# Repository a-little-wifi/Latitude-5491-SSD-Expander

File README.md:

# Latitude 5491 SSD Expander
This project is a PCB meant to fit in the large empty space around the Dell Latitude 5491's M.2 SSD slot. Together with a firmware modification, it should allow me to fit 2 2280 NVMe SSDs with 2 PCIe lanes each.

This is also an experiment to figure out PCIe bifurcation in general. In this case I'm using a Renesas 9ZXL0651AKLF clock buffer with 6 outputs, but I'm only using the first 2 for this board.

Should in theory also work on the H-class CPU version of the Latitude 5480, but not the U-class 5480 and 5490, those only have 2 PCIe lanes for the SSD slot in the first place.

~~Impedance is tuned for Aisler's 4-layer 0.8mm process~~ (thanks [Aisler](https://aisler.net/) for sponsoring the fabrication of this board!)  
Turns out the impedance and possibly other factors are not quite right, the current design has issues maintaining the PCIe link on the first slot, be aware if you plan to use this design.

### pics:

> 
> 

> 
> 

# Results:

## It works!
> 

> Bifurcation board with 2 SSDs installed in a Latitude 5491

> 

> Both SSDs showing up in the setup menu (the second one is showing in the entry usually meant for the WWAN slot lol)

> 

> Both SSDs detected in Gnome Disks (Ubuntu 16.04 live)

> 

> Both SSDs showing up in lspci (not shown: both running at PCIe x2 as expected)

## How to make it work:

To get this working, you need to modify the Flex I/O configuration of your laptop by dumping the content of the BIOS chip, loading it into Intel's Flash Image Tool (mfit) (version 12.0.85.1919 for the Latitude 5491), navigating to the Flex I/O section and changing the PCIe Port Configuration for PCIe Controller 3 (Port 9-12) (this is the one connected to the M-key slot on the 5491) from 1x4 to 2x2:

> 

> Changing the PCIe port from 1x4 to 2x2 in mfit

Then click the Build Image button at the top of the mfit window to generate a new bios binary file that can be flashed back onto the laptop (outimage.bin in the same directory as fit.exe)

For your first boot you might need to clear the cmos to get it to run and also give it a few reboot cycles. 

## I provide no warranty on any of this, I am not responsible if you mess up your machine  
This is only an experiment to prove it's possible for end users to bifurcate and generally change the configuration of the PCH PCIe lanes in their Intel-based laptop

For the next bifurcation adapter I'll probably use the Renesas 9DBL411BGLFT clock buffer instead, looks easier to solder and is readily available

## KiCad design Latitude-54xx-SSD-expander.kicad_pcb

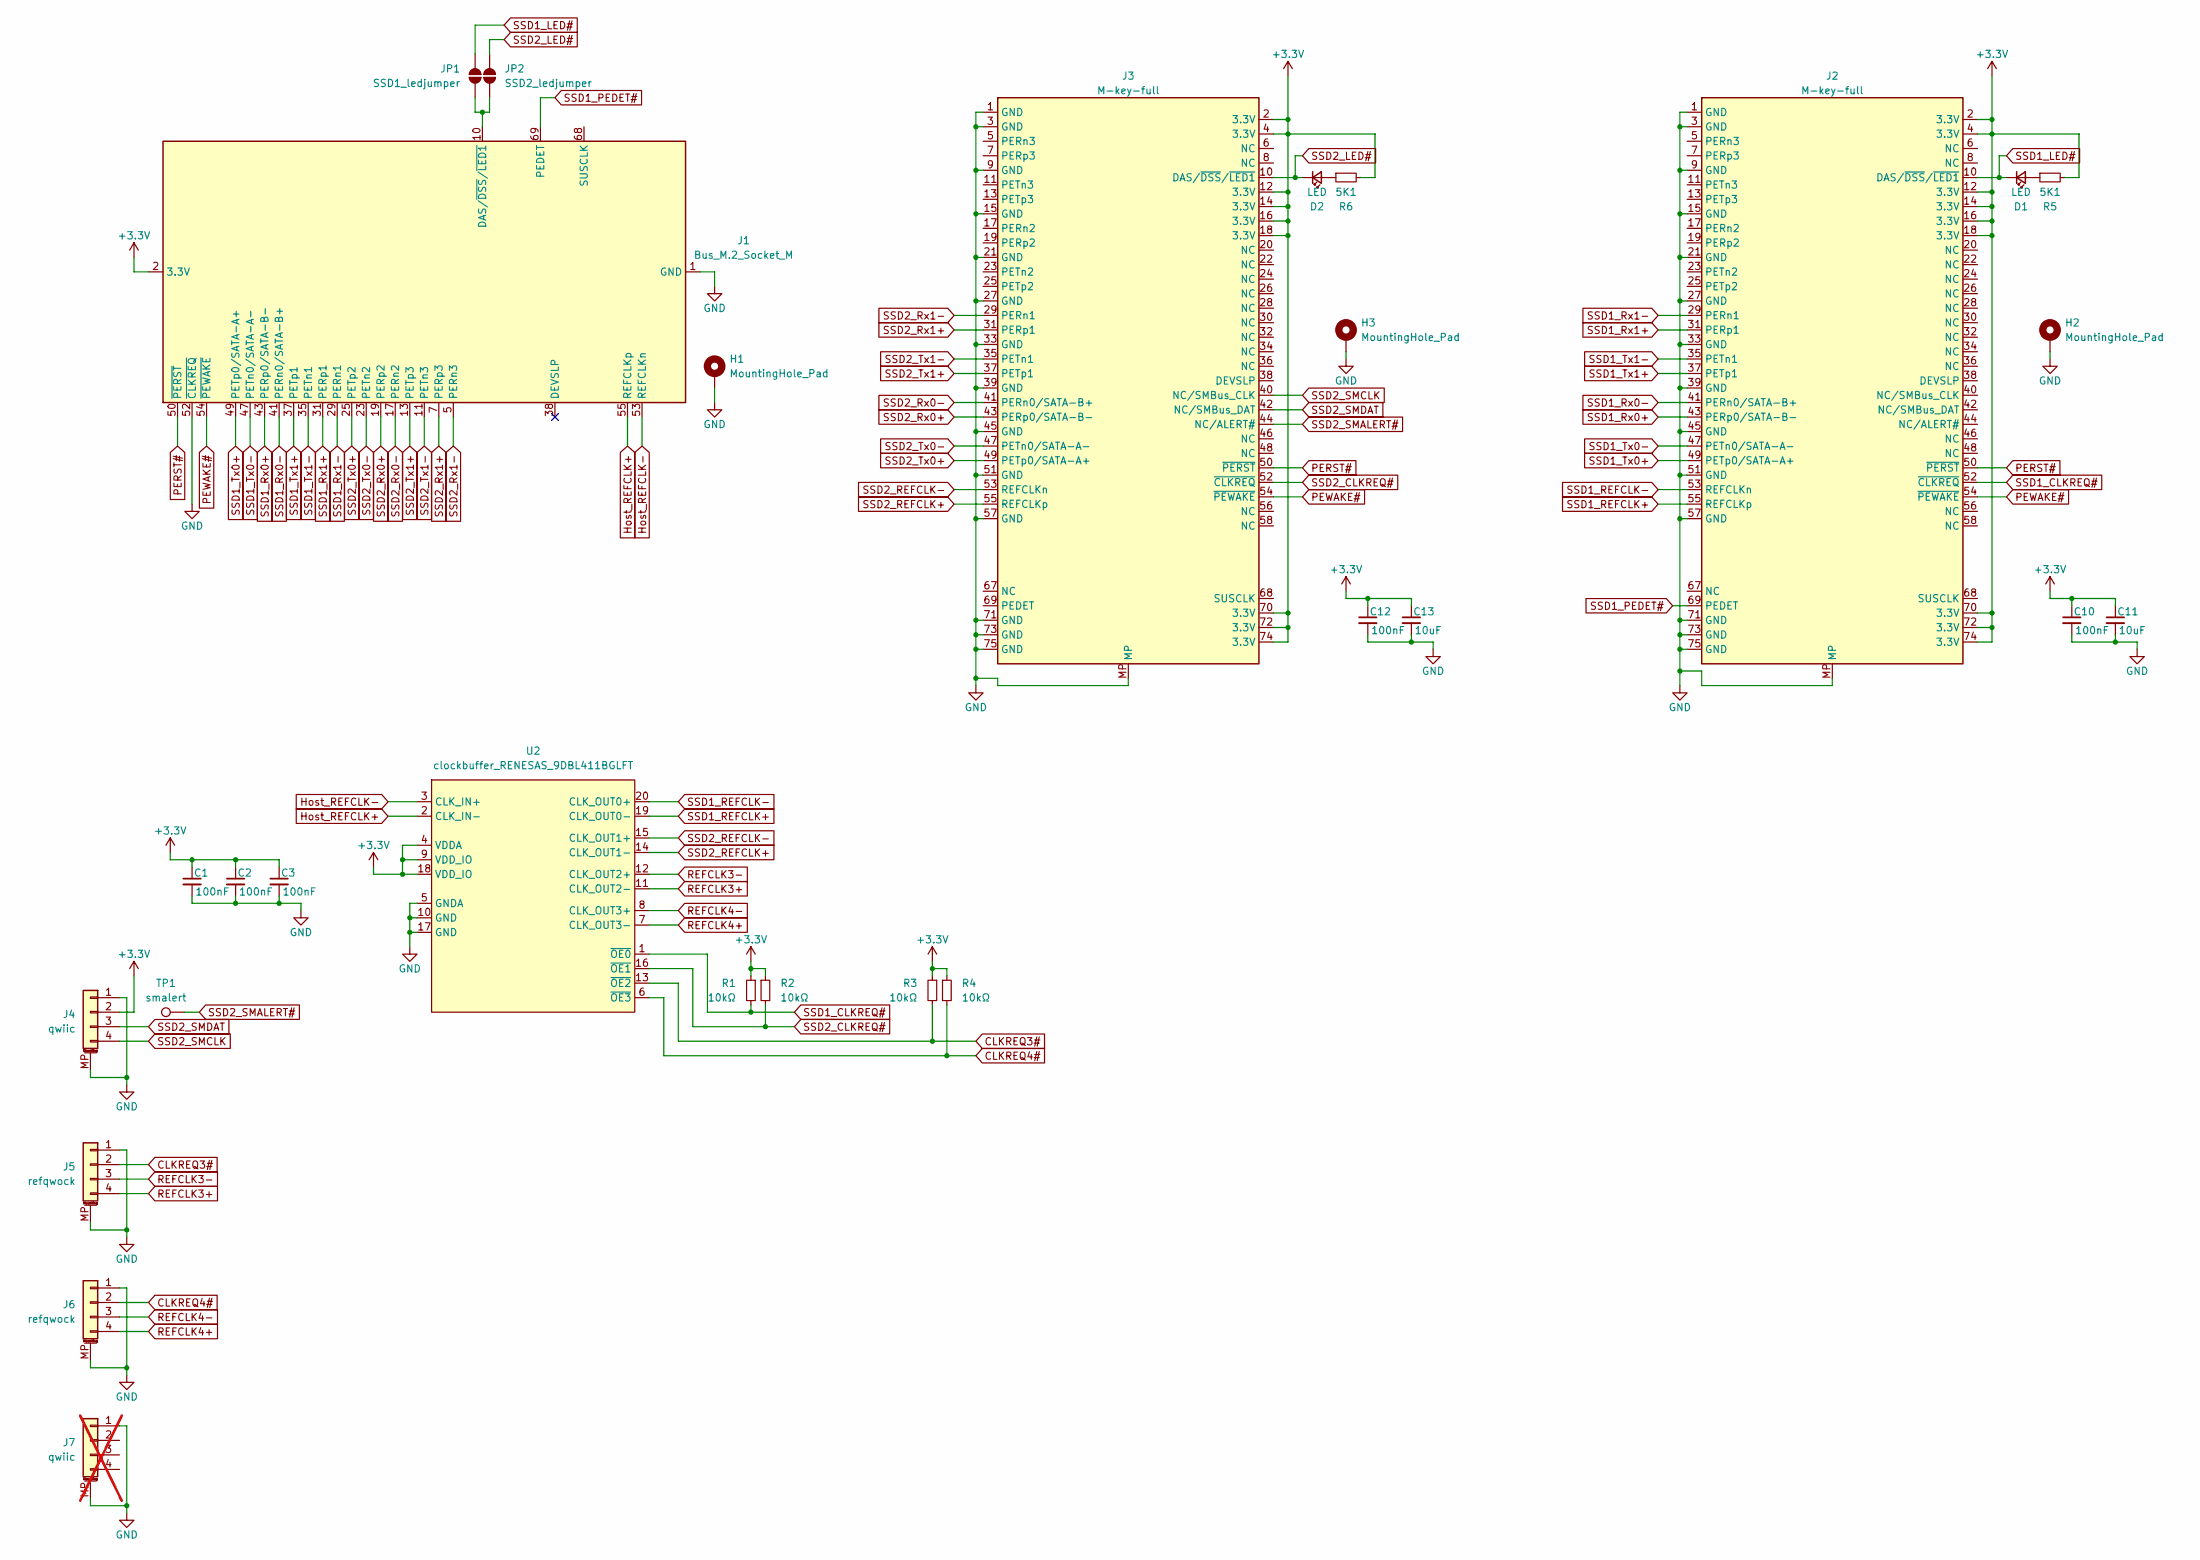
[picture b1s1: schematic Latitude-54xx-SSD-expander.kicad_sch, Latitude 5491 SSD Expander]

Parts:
C1, C2, C3, C10, C12: 100nF; C_0603_1608Metric
C11, C13: 10uF; C_0603_1608Metric
D1, D2: LED; D_0603_1608Metric
H1: MountingHole_Pad; MountingHole_3.5mm_Pad
H2, H3: MountingHole_Pad; MountingHole_4mm_Pad
J1: Bus_M.2_Socket_M; NGFF_M
J2, J3: M-key-full; m-key
J4: qwiic; JST_SH_SM04B-SRSS-TB_1x04-1MP_P1.00mm_Horizontal
J5, J6: refqwock; JST_SH_SM04B-SRSS-TB_1x04-1MP_P1.00mm_Horizontal
J7: qwiic; JST_SH_SM04B-SRSS-TB_1x04-1MP_P1.00mm_Horizontal; not fitted
JP1: SSD1_ledjumper; mySolderJumper-1x0.5mm
JP2: SSD2_ledjumper; mySolderJumper-1x0.5mm
R1, R2, R3, R4: 10kΩ; R_0603_1608Metric
R5, R6: 5K1; R_0603_1608Metric
TP1: smalert; TestPoint_Pad_D1.0mm
U2: clockbuffer_RENESAS_9DBL411BGLFT; clockbuffer_RENESAS 9DBL411BGLFT; LCSC Part C2649348

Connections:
+3.3V: C1.1, C2.1, C3.1, C10.1, C11.1, C12.1, C13.1, J1.2 (3.3V), J1.4 (3.3V), J1.12 (3.3V), J1.14 (3.3V), J1.16 (3.3V), J1.18 (3.3V), J1.70 (3.3V), J1.72 (3.3V), J1.74 (3.3V), J2.2 (3.3V), J2.4 (3.3V), J2.12 (3.3V), J2.14 (3.3V), J2.16 (3.3V), J2.18 (3.3V), J2.70 (3.3V), J2.72 (3.3V), J2.74 (3.3V), J3.2 (3.3V), J3.4 (3.3V), J3.12 (3.3V), J3.14 (3.3V), J3.16 (3.3V), J3.18 (3.3V), J3.70 (3.3V), J3.72 (3.3V), J3.74 (3.3V), J4.2, R1.1, R2.1, R3.1, R4.1, R5.2, R6.2, U2.4 (VDDA), U2.9 (VDD_IO), U2.18 (VDD_IO)
CLKREQ3#: J5.2, R3.2, U2.13 (~OE2)
CLKREQ4#: J6.2, R4.2, U2.6 (~OE3)
GND: C1.2, C2.2, C3.2, C10.2, C11.2, C12.2, C13.2, H1.1, H2.1, H3.1, J1.1 (GND), J1.3 (GND), J1.9 (GND), J1.15 (GND), J1.21 (GND), J1.27 (GND), J1.33 (GND), J1.39 (GND), J1.45 (GND), J1.51 (GND), J1.52 (~CLKREQ), J1.57 (GND), J1.71 (GND), J1.73 (GND), J1.75 (GND), J2.1 (GND), J2.3 (GND), J2.9 (GND), J2.15 (GND), J2.21 (GND), J2.27 (GND), J2.33 (GND), J2.39 (GND), J2.45 (GND), J2.51 (GND), J2.57 (GND), J2.71 (GND), J2.73 (GND), J2.75 (GND), J2.MP, J3.1 (GND), J3.3 (GND), J3.9 (GND), J3.15 (GND), J3.21 (GND), J3.27 (GND), J3.33 (GND), J3.39 (GND), J3.45 (GND), J3.51 (GND), J3.57 (GND), J3.71 (GND), J3.73 (GND), J3.75 (GND), J3.MP, J4.1, J4.MP (MountPin), J5.1, J5.MP (MountPin), J6.1, J6.MP (MountPin), J7.1, J7.MP (MountPin), U2.5 (GNDA), U2.10 (GND), U2.17 (GND)
Host_REFCLK+: J1.55 (REFCLKp), U2.2 (CLK_IN-)
Host_REFCLK-: J1.53 (REFCLKn), U2.3 (CLK_IN+)
unnamed: D1.2 (A), R5.1
unnamed: D2.2 (A), R6.1
unnamed: J1.10 (DAS/~DSS/~LED1), JP1.1 (A), JP2.1 (A)
PERST#: J1.50 (~PERST), J2.50 (~PERST), J3.50 (~PERST)
PEWAKE#: J1.54 (~PEWAKE), J2.54 (~PEWAKE), J3.54 (~PEWAKE)
REFCLK3+: J5.4, U2.11 (CLK_OUT2-)
REFCLK3-: J5.3, U2.12 (CLK_OUT2+)
REFCLK4+: J6.4, U2.7 (CLK_OUT3-)
REFCLK4-: J6.3, U2.8 (CLK_OUT3+)
SSD1_CLKREQ#: J2.52 (~CLKREQ), R1.2, U2.1 (~OE0)
SSD1_LED#: D1.1 (K), J2.10 (DAS/~DSS/~LED1), JP1.2 (B)
SSD1_PEDET#: J1.69 (PEDET), J2.69 (PEDET)
SSD1_REFCLK+: J2.55 (REFCLKp), U2.19 (CLK_OUT0-)
SSD1_REFCLK-: J2.53 (REFCLKn), U2.20 (CLK_OUT0+)
SSD1_Rx0+: J1.43 (PERp0/SATA-B-), J2.43 (PERp0/SATA-B-)
SSD1_Rx0-: J1.41 (PERn0/SATA-B+), J2.41 (PERn0/SATA-B+)
SSD1_Rx1+: J1.31 (PERp1), J2.31 (PERp1)
SSD1_Rx1-: J1.29 (PERn1), J2.29 (PERn1)
SSD1_Tx0+: J1.49 (PETp0/SATA-A+), J2.49 (PETp0/SATA-A+)
SSD1_Tx0-: J1.47 (PETn0/SATA-A-), J2.47 (PETn0/SATA-A-)
SSD1_Tx1+: J1.37 (PETp1), J2.37 (PETp1)
SSD1_Tx1-: J1.35 (PETn1), J2.35 (PETn1)
SSD2_CLKREQ#: J3.52 (~CLKREQ), R2.2, U2.16 (~OE1)
SSD2_LED#: D2.1 (K), J3.10 (DAS/~DSS/~LED1), JP2.2 (B)
SSD2_REFCLK+: J3.55 (REFCLKp), U2.14 (CLK_OUT1-)
SSD2_REFCLK-: J3.53 (REFCLKn), U2.15 (CLK_OUT1+)
SSD2_Rx0+: J1.19 (PERp2), J3.43 (PERp0/SATA-B-)
SSD2_Rx0-: J1.17 (PERn2), J3.41 (PERn0/SATA-B+)
SSD2_Rx1+: J1.7 (PERp3), J3.31 (PERp1)
SSD2_Rx1-: J1.5 (PERn3), J3.29 (PERn1)
SSD2_SMALERT#: J3.44 (NC/ALERT#), TP1.1
SSD2_SMCLK: J3.40 (NC/SMBus_CLK), J4.4
SSD2_SMDAT: J3.42 (NC/SMBus_DAT), J4.3
SSD2_Tx0+: J1.25 (PETp2), J3.49 (PETp0/SATA-A+)
SSD2_Tx0-: J1.23 (PETn2), J3.47 (PETn0/SATA-A-)
SSD2_Tx1+: J1.13 (PETp3), J3.37 (PETp1)
SSD2_Tx1-: J1.11 (PETn3), J3.35 (PETn1)

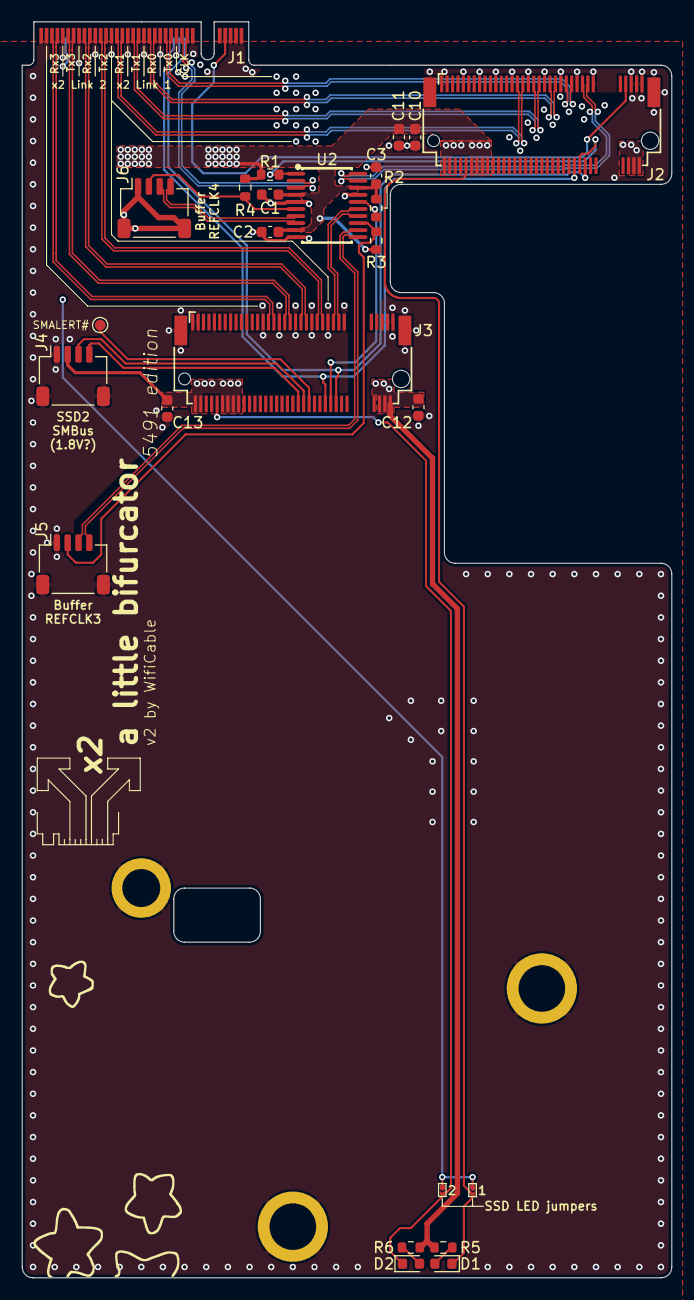
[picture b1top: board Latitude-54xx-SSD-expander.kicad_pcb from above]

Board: 4 copper layers, 60.0 x 116.0 mm, 28 parts (0 on the bottom side), 43 nets.

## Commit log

2024-09-13 Added files
2024-09-13 Wrote a simple readme
2024-09-13 Adjusted line thickness for printing
2024-09-14 Rearranged schematic for readability
2024-09-14 Added compatibility note
2024-09-14 brick :3
2024-09-14 logo concept on the silkscreen
2024-09-14 Silkscreen adjustments
2024-09-14 Added pictures
2024-09-14 Adjusted readme picture layout
2024-09-14 Added todo list
2024-09-16 Added capacitors for m.2 slots and ground vias for pcie
2024-09-18 fixed m.2 slot refdes
2024-09-21 Added activity leds
2024-09-28 led placement and traces
    this was supposed to already be there???
2024-10-28 Added hole for Dell's silly mount
2024-10-28 Lots of small fixes to prepare for production
    more ground vias,, fixed a diffpair reference layer issue
2024-10-28 Added i2c pullups
2024-10-28 page note
2024-10-28 edge vias
    for some reason, they probably look cool
2024-10-28 Added user defined bridges for aisler
    They're on layer user 3, move to edge.cuts to use them
2025-04-15 Added experiment results
2025-04-15 Adjusted image formatting
2025-04-15 Clarified the instructions are for the 5491
2025-04-15 Added note about better clock buffer
2025-05-26 Connected PEDET for first slot
2025-06-13 Added fabrication process note
2026-02-21 Added first slot link issues warning
2026-03-05 v2
    replaced buffer with 9DBL411BGLFT, fixed impedance (for JLC), added spare refclk breakouts, added ssd smbus breakout, added host activity LED option, improved PCIe pair layout. todo: fix standoff foo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
2026-03-05 Minor tweaks
    Added pinouts to silkscreen
2026-03-06 fixed m.2 standoff footprints, v2 done?
2026-03-06 fixed m.2 standoff footprint for real this time
2026-03-06 changed led jumpers to custom solderjumpers
2026-03-06 more small tweaks
2026-03-06 More minor changes!
    final final version fr copy(3) last one finished definitely done now™️
2026-06-15 moar ground vias
